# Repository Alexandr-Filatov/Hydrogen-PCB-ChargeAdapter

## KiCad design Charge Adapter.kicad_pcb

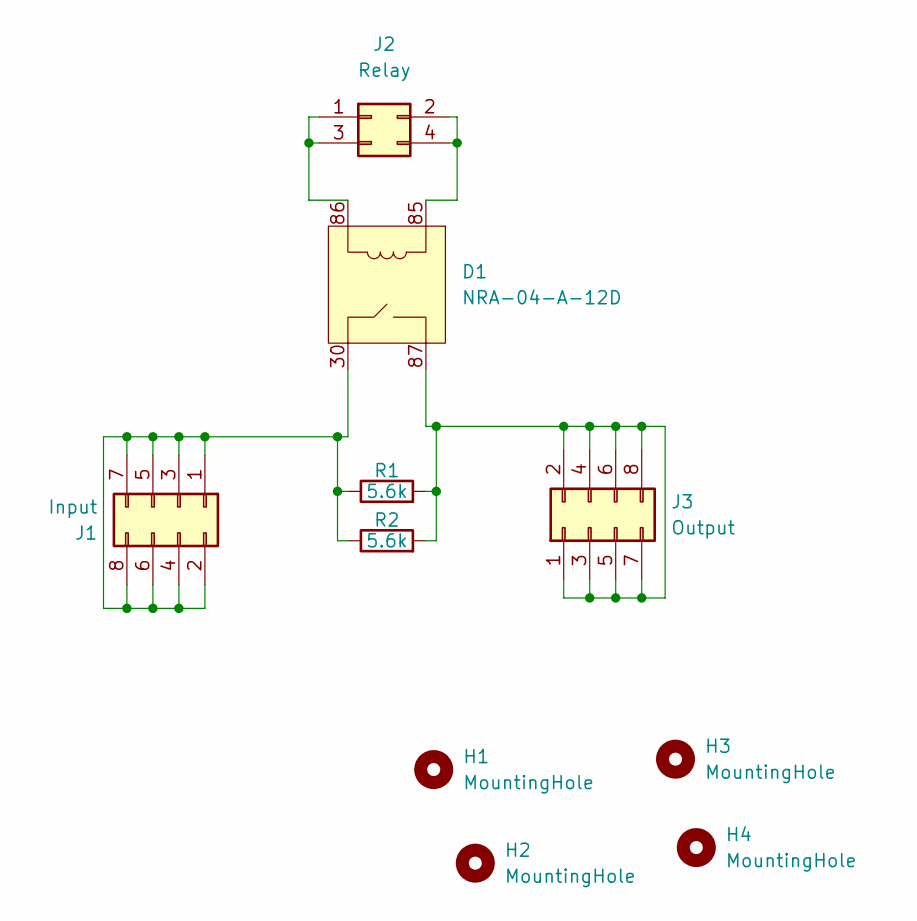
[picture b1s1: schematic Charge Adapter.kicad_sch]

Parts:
D1: NRA-04-A-12D
H1, H2, H3, H4: MountingHole; MountingHole_3.2mm_M3
J1: Input; Molex_Micro-Fit_3.0_43045-0800_2x04_P3.00mm_Horizontal
J2: Relay; Molex_Micro-Fit_3.0_43045-0400_2x02_P3.00mm_Horizontal
J3: Output; Molex_Micro-Fit_3.0_43045-0800_2x04_P3.00mm_Horizontal
R1, R2: 5.6k; R_Axial_Power_L48.0mm_W12.5mm_P60.96mm

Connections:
unnamed: D1.30, J1.1, J1.2, J1.3, J1.4, J1.5, J1.6, J1.7, J1.8, R1.1, R2.1
unnamed: D1.85, J2.2, J2.4
unnamed: D1.86, J2.1, J2.3
unnamed: D1.87, J3.1, J3.2, J3.3, J3.4, J3.5, J3.6, J3.7, J3.8, R1.2, R2.2

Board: 2 copper layers, 10 parts (0 on the bottom side), 4 nets, no tracks yet.

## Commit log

2022-06-02 Первая версия в производство
